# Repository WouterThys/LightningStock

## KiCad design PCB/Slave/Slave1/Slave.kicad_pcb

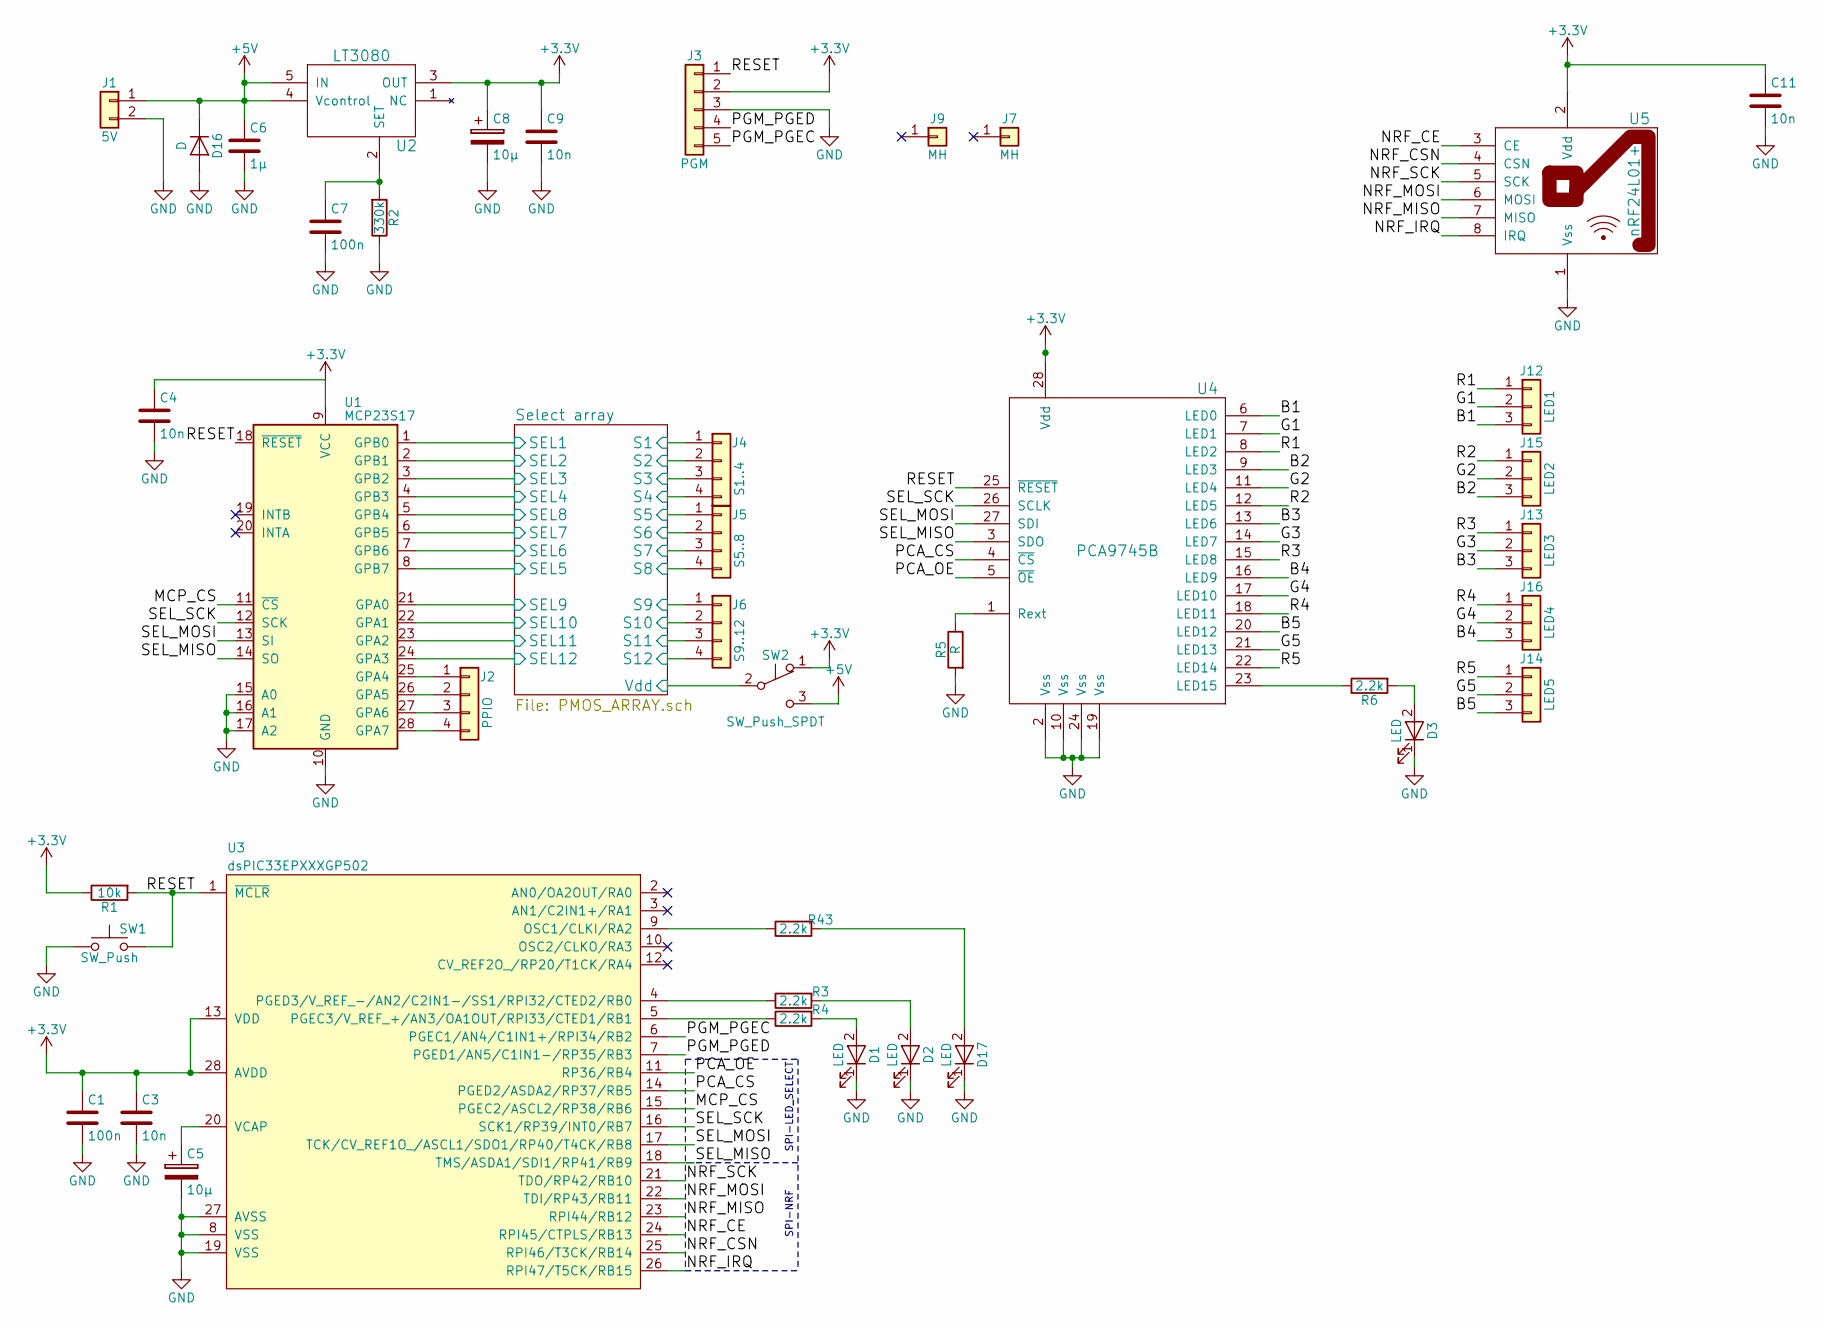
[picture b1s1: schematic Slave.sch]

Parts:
C1, C7: 100n; C_0603_HandSoldering
C3, C4, C9, C11: 10n; C_0603_HandSoldering
C5, C8: 10µ; CP_Tantalum_Case-A_EIA-3216-18_Reflow
C6: 1µ; C_0603_HandSoldering
D1, D2, D3, D17: LED; LED_0603_HandSoldering
D16: D; D_MicroMELF_Hadsoldering
J1: 5V; Pin_Header_Straight_1x02_Pitch2.54mm
J2: PPIO; Pin_Header_Straight_1x04_Pitch2.54mm
J3: PGM; Pin_Header_Angled_1x05_Pitch2.54mm
J4: S1..4; Pin_Header_Straight_1x04_Pitch2.54mm
J5: S5..8; Pin_Header_Straight_1x04_Pitch2.54mm
J6: S9..12; Pin_Header_Straight_1x04_Pitch2.54mm
J7, J9: MH; MountingHole_2.7mm_M2.5_ISO14580_Pad
J12: LED1; Molex_PicoBlade_53047-0310_03x1.25mm_Straight
J13: LED3; Molex_PicoBlade_53047-0310_03x1.25mm_Straight
J14: LED5; Molex_PicoBlade_53047-0310_03x1.25mm_Straight
J15: LED2; Molex_PicoBlade_53047-0310_03x1.25mm_Straight
J16: LED4; Molex_PicoBlade_53047-0310_03x1.25mm_Straight
R1: 10k; R_0603_HandSoldering
R2: 330k; R_0603_HandSoldering
R3, R4, R6, R43: 2.2k; R_0603_HandSoldering
R5: R; R_0603_HandSoldering
SW1: SW_Push; SW_PUSH_6mm
SW2: SW_Push_SPDT; Pin_Header_Straight_1x03_Pitch2.54mm
U1: MCP23S17; SOIC-28W_7.5x17.9mm_Pitch1.27mm
U2: LT3080; TO-220-5_Vertical_StaggeredType1
U3: dsPIC33EPXXXGP502; SOIC-28W_7.5x17.9mm_Pitch1.27mm
U4: PCA9745B; TSSOP-28_4.4x9.7mm_Pitch0.65mm
U5: nRF24L01+; Pin_Header_Straight_2x04_Pitch2.54mm

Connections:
+3V3: C1.1, C3.1, C4.1, C8.1, C9.1, C11.1, J3.2, R1.1, SW2.1 (A), U1.9 (VCC), U2.3 (OUT), U3.13 (VDD), U3.28 (AVDD), U4.28 (Vdd), U5.2 (Vdd); also elsewhere on the board
+5V: C6.1, D16.1 (K), J1.1, SW2.3 (C), U2.4 (Vcontrol), U2.5 (IN); also elsewhere on the board
/B1: J12.3, U4.6 (LED0)
/B2: J15.3, U4.9 (LED3)
/B3: J13.3, U4.13 (LED6)
/B4: J16.3, U4.16 (LED9)
/B5: J14.3, U4.20 (LED12)
/G1: J12.2, U4.7 (LED1)
/G2: J15.2, U4.11 (LED4)
/G3: J13.2, U4.14 (LED7)
/G4: J16.2, U4.17 (LED10)
/G5: J14.2, U4.21 (LED13)
/MCP_CS: U1.11 (~CS), U3.15 (PGEC2/ASCL2/RP38/RB6)
/NRF_CE: U3.24 (RPI45/CTPLS/RB13), U5.3 (CE)
/NRF_CSN: U3.25 (RPI46/T3CK/RB14), U5.4 (CSN)
/NRF_IRQ: U3.26 (RPI47/T5CK/RB15), U5.8 (IRQ)
/NRF_MISO: U3.23 (RPI44/RB12), U5.7 (MISO)
/NRF_MOSI: U3.22 (TDI/RP43/RB11), U5.6 (MOSI)
/NRF_SCK: U3.21 (TDO/RP42/RB10), U5.5 (SCK)
/PCA_CS: U3.14 (PGED2/ASDA2/RP37/RB5), U4.4 (~CS)
/PCA_OE: U3.11 (RP36/RB4), U4.5 (~OE)
/PGM_PGEC: J3.5, U3.6 (PGEC1/AN4/C1IN1+/RPI34/RB2)
/PGM_PGED: J3.4, U3.7 (PGED1/AN5/C1IN1-/RP35/RB3)
/R1: J12.1, U4.8 (LED2)
/R2: J15.1, U4.12 (LED5)
/R3: J13.1, U4.15 (LED8)
/R4: J16.1, U4.18 (LED11)
/R5: J14.1, U4.22 (LED14)
/RESET: J3.1, R1.2, SW1.2, U1.18 (~RESET), U3.1 (~MCLR), U4.25 (~RESET)
/SEL_MISO: U1.14 (SO), U3.18 (TMS/ASDA1/SDI1/RP41/RB9), U4.3 (SDO)
/SEL_MOSI: U1.13 (SI), U3.17 (TCK/CV_REF1O_/ASCL1/SDO1/RP40/T4CK/RB8), U4.27 (SDI)
/SEL_SCK: U1.12 (SCK), U3.16 (SCK1/RP39/INT0/RB7), U4.26 (SCLK)
/Select array/S1: J4.1; also elsewhere on the board
/Select array/S2: J4.2; also elsewhere on the board
/Select array/S3: J4.3; also elsewhere on the board
/Select array/S4: J4.4; also elsewhere on the board
/Select array/S5: J5.1; also elsewhere on the board
/Select array/S6: J5.2; also elsewhere on the board
/Select array/S7: J5.3; also elsewhere on the board
/Select array/S8: J5.4; also elsewhere on the board
/Select array/S9: J6.1; also elsewhere on the board
/Select array/S10: J6.2; also elsewhere on the board
/Select array/S11: J6.3; also elsewhere on the board
/Select array/S12: J6.4; also elsewhere on the board
/Select array/SEL1: U1.1 (GPB0); also elsewhere on the board
/Select array/SEL2: U1.2 (GPB1); also elsewhere on the board
/Select array/SEL3: U1.3 (GPB2); also elsewhere on the board
/Select array/SEL4: U1.4 (GPB3); also elsewhere on the board
/Select array/SEL5: U1.8 (GPB7); also elsewhere on the board
/Select array/SEL6: U1.7 (GPB6); also elsewhere on the board
/Select array/SEL7: U1.6 (GPB5); also elsewhere on the board
/Select array/SEL8: U1.5 (GPB4); also elsewhere on the board
/Select array/SEL9: U1.21 (GPA0); also elsewhere on the board
/Select array/SEL10: U1.22 (GPA1); also elsewhere on the board
/Select array/SEL11: U1.23 (GPA2); also elsewhere on the board
/Select array/SEL12: U1.24 (GPA3); also elsewhere on the board
GND: C1.2, C3.2, C4.2, C5.2, C6.2, C7.2, C8.2, C9.2, C11.2, D1.1 (K), D2.1 (K), D3.1 (K), D16.2 (A), D17.1 (K), J1.2, J3.3, R2.1, R5.2, SW1.1, U1.10 (GND), U1.15 (A0), U1.16 (A1), U1.17 (A2), U3.8 (VSS), U3.19 (VSS), U3.27 (AVSS), U4.2 (Vss), U4.10 (Vss), U4.19 (Vss), U4.24 (Vss), U5.1 (Vss); also elsewhere on the board
unnamed: C5.1, U3.20 (VCAP)
unnamed: C7.1, R2.2, U2.2 (SET)
unnamed: D1.2 (A), R4.2
unnamed: D2.2 (A), R3.2
unnamed: D3.2 (A), R6.2
unnamed: D17.2 (A), R43.2
unnamed: J2.1, U1.25 (GPA4)
unnamed: J2.2, U1.26 (GPA5)
unnamed: J2.3, U1.27 (GPA6)
unnamed: J2.4, U1.28 (GPA7)
unnamed: R3.1, U3.4 (PGED3/V_REF_-/AN2/C2IN1-/SS1/RPI32/CTED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)
unnamed: R4.1, U3.5 (PGEC3/V_REF_+/AN3/OA1OUT/RPI33/CTED1/RB1)
unnamed: R5.1, U4.1 (Rext)
unnamed: R6.1, U4.23 (LED15)
unnamed: R43.1, U3.9 (OSC1/CLKI/RA2)

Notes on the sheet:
SPI-LED_SELECT
SPI-NRF

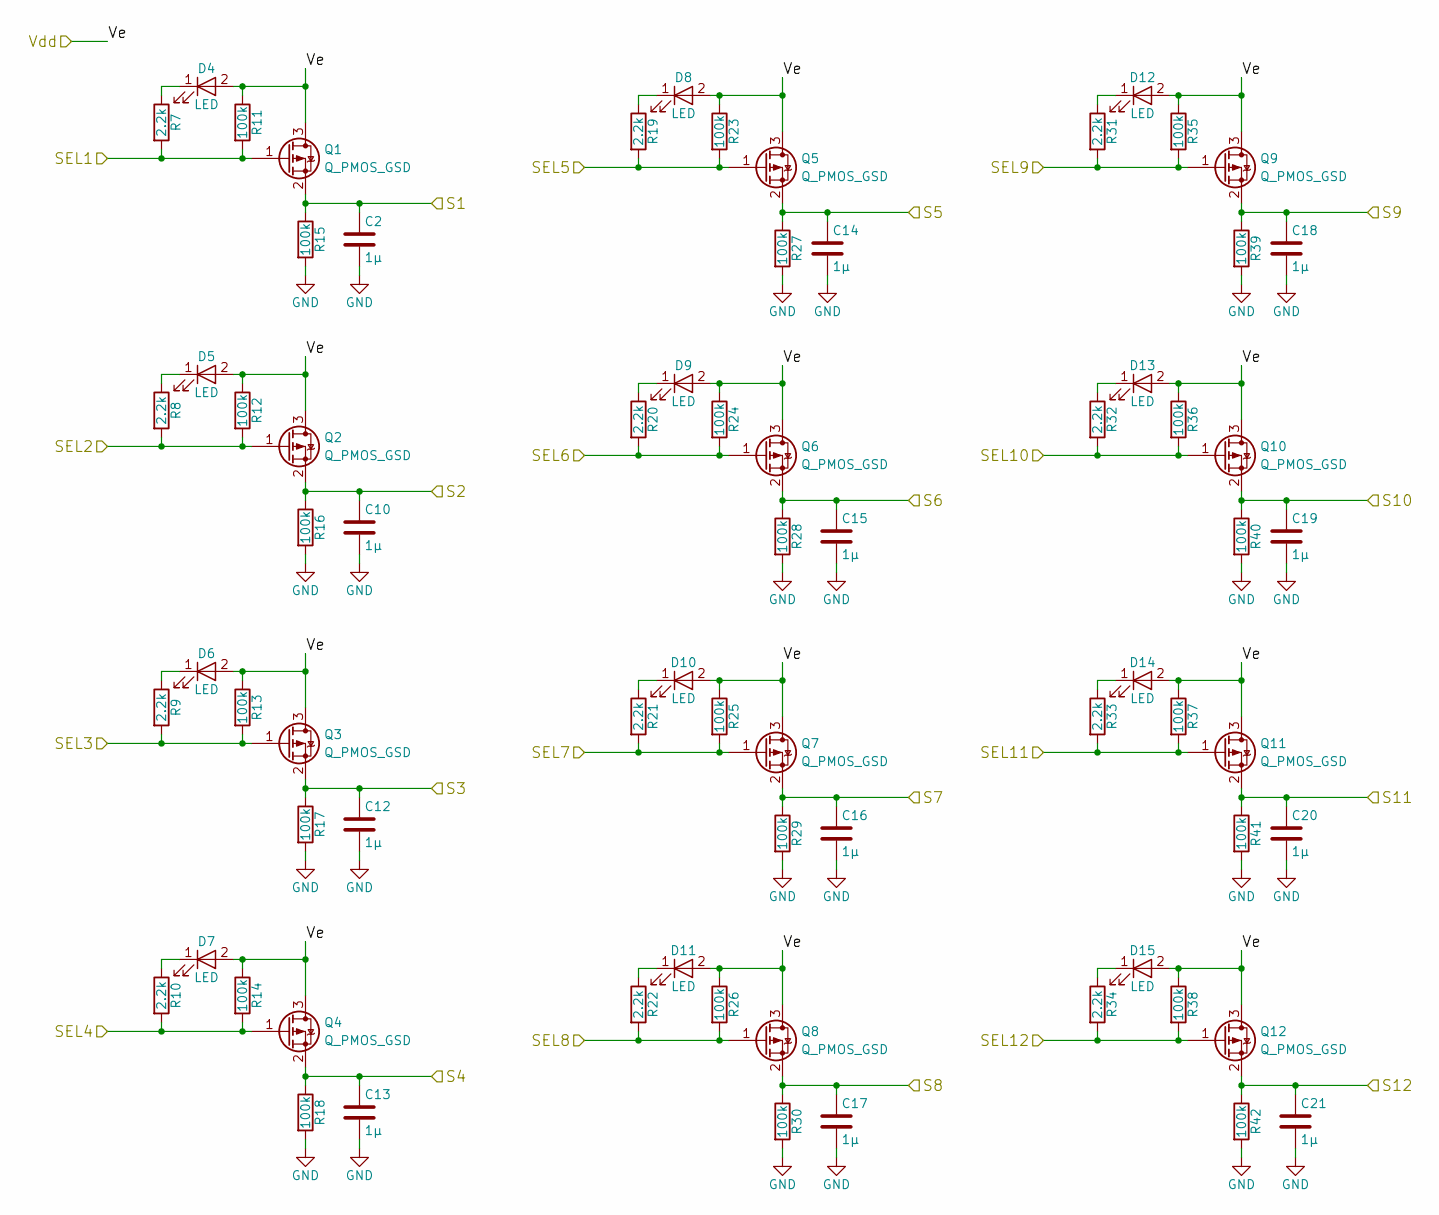
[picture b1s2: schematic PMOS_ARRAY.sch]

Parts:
C2, C10, C12, C13, C14, C15, C16, C17, C18, C19, C20, C21: 1µ; C_0603_HandSoldering
D4, D5, D6, D7, D8, D9, D10, D11, D12, D13, D14, D15: LED; LED_0603_HandSoldering
Q1, Q2, Q3, Q4, Q5, Q6, Q7, Q8, Q9, Q10, Q11, Q12: Q_PMOS_GSD; SOT-323_SC-70_Handsoldering
R7, R8, R9, R10, R19, R20, R21, R22, R31, R32, R33, R34: 2.2k; R_0603_HandSoldering
R11, R12, R13, R14, R15, R16, R17, R18, R23, R24, R25, R26, R27, R28, R29, R30, R35, R36, R37, R38, R39, R40, R41, R42: 100k; R_0603_HandSoldering

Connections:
/Select array/S1: C2.1, Q1.2 (S), R15.1; also elsewhere on the board
/Select array/S2: C10.1, Q2.2 (S), R16.1; also elsewhere on the board
/Select array/S3: C12.1, Q3.2 (S), R17.1; also elsewhere on the board
/Select array/S4: C13.1, Q4.2 (S), R18.1; also elsewhere on the board
/Select array/S5: C14.1, Q5.2 (S), R27.1; also elsewhere on the board
/Select array/S6: C15.1, Q6.2 (S), R28.1; also elsewhere on the board
/Select array/S7: C16.1, Q7.2 (S), R29.1; also elsewhere on the board
/Select array/S8: C17.1, Q8.2 (S), R30.1; also elsewhere on the board
/Select array/S9: C18.1, Q9.2 (S), R39.1; also elsewhere on the board
/Select array/S10: C19.1, Q10.2 (S), R40.1; also elsewhere on the board
/Select array/S11: C20.1, Q11.2 (S), R41.1; also elsewhere on the board
/Select array/S12: C21.1, Q12.2 (S), R42.1; also elsewhere on the board
/Select array/SEL1: Q1.1 (G), R7.2, R11.2; also elsewhere on the board
/Select array/SEL2: Q2.1 (G), R8.2, R12.2; also elsewhere on the board
/Select array/SEL3: Q3.1 (G), R9.2, R13.2; also elsewhere on the board
/Select array/SEL4: Q4.1 (G), R10.2, R14.2; also elsewhere on the board
/Select array/SEL5: Q5.1 (G), R19.2, R23.2; also elsewhere on the board
/Select array/SEL6: Q6.1 (G), R20.2, R24.2; also elsewhere on the board
/Select array/SEL7: Q7.1 (G), R21.2, R25.2; also elsewhere on the board
/Select array/SEL8: Q8.1 (G), R22.2, R26.2; also elsewhere on the board
/Select array/SEL9: Q9.1 (G), R31.2, R35.2; also elsewhere on the board
/Select array/SEL10: Q10.1 (G), R32.2, R36.2; also elsewhere on the board
/Select array/SEL11: Q11.1 (G), R33.2, R37.2; also elsewhere on the board
/Select array/SEL12: Q12.1 (G), R34.2, R38.2; also elsewhere on the board
/Select array/Vdd: D4.2 (A), D5.2 (A), D6.2 (A), D7.2 (A), D8.2 (A), D9.2 (A), D10.2 (A), D11.2 (A), D12.2 (A), D13.2 (A), D14.2 (A), D15.2 (A), Q1.3 (D), Q2.3 (D), Q3.3 (D), Q4.3 (D), Q5.3 (D), Q6.3 (D), Q7.3 (D), Q8.3 (D), Q9.3 (D), Q10.3 (D), Q11.3 (D), Q12.3 (D), R11.1, R12.1, R13.1, R14.1, R23.1, R24.1, R25.1, R26.1, R35.1, R36.1, R37.1, R38.1; also elsewhere on the board
GND: C2.2, C10.2, C12.2, C13.2, C14.2, C15.2, C16.2, C17.2, C18.2, C19.2, C20.2, C21.2, R15.2, R16.2, R17.2, R18.2, R27.2, R28.2, R29.2, R30.2, R39.2, R40.2, R41.2, R42.2; also elsewhere on the board
unnamed: D4.1 (K), R7.1
unnamed: D5.1 (K), R8.1
unnamed: D6.1 (K), R9.1
unnamed: D7.1 (K), R10.1
unnamed: D8.1 (K), R19.1
unnamed: D9.1 (K), R20.1
unnamed: D10.1 (K), R21.1
unnamed: D11.1 (K), R22.1
unnamed: D12.1 (K), R31.1
unnamed: D13.1 (K), R32.1
unnamed: D14.1 (K), R33.1
unnamed: D15.1 (K), R34.1

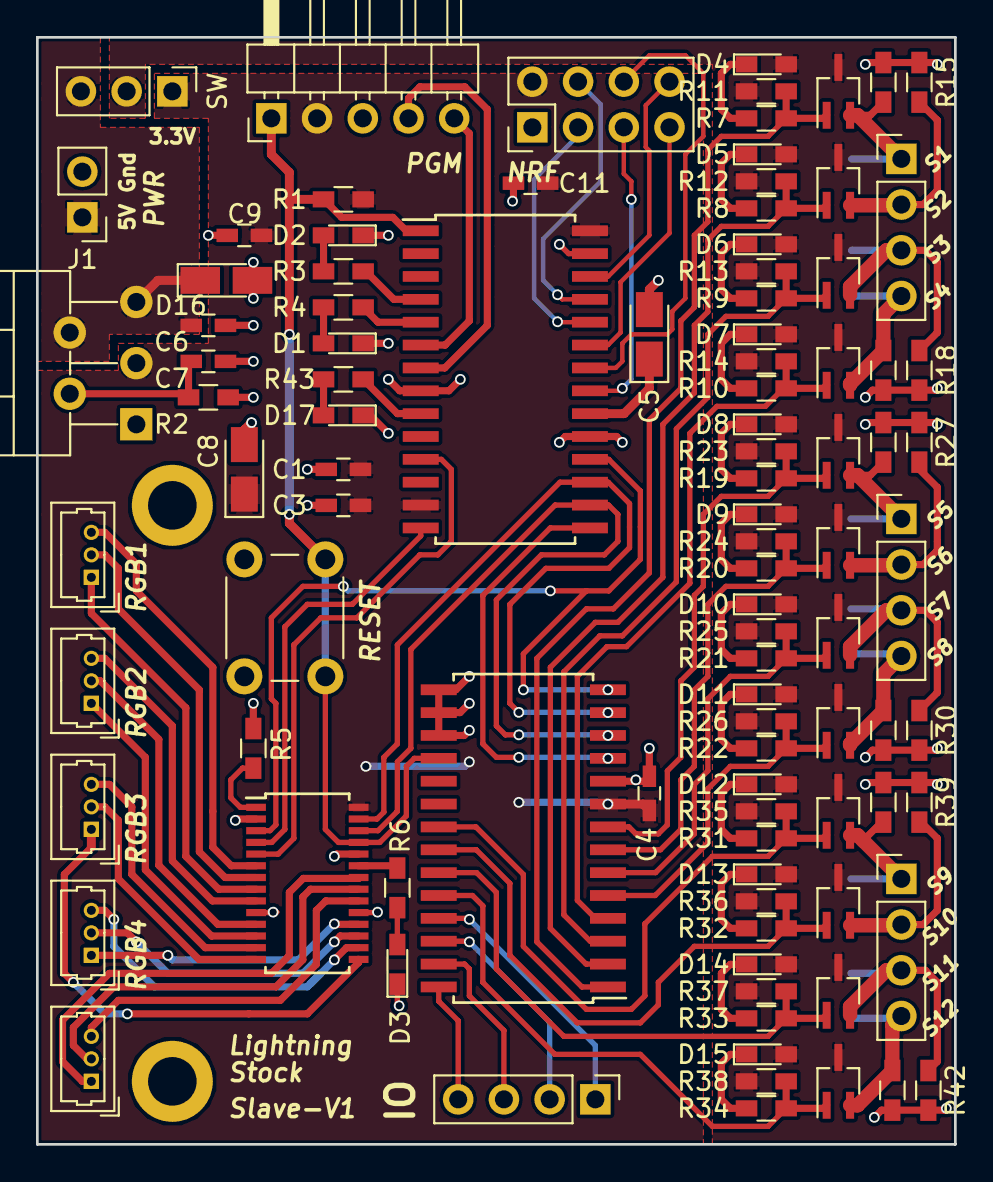
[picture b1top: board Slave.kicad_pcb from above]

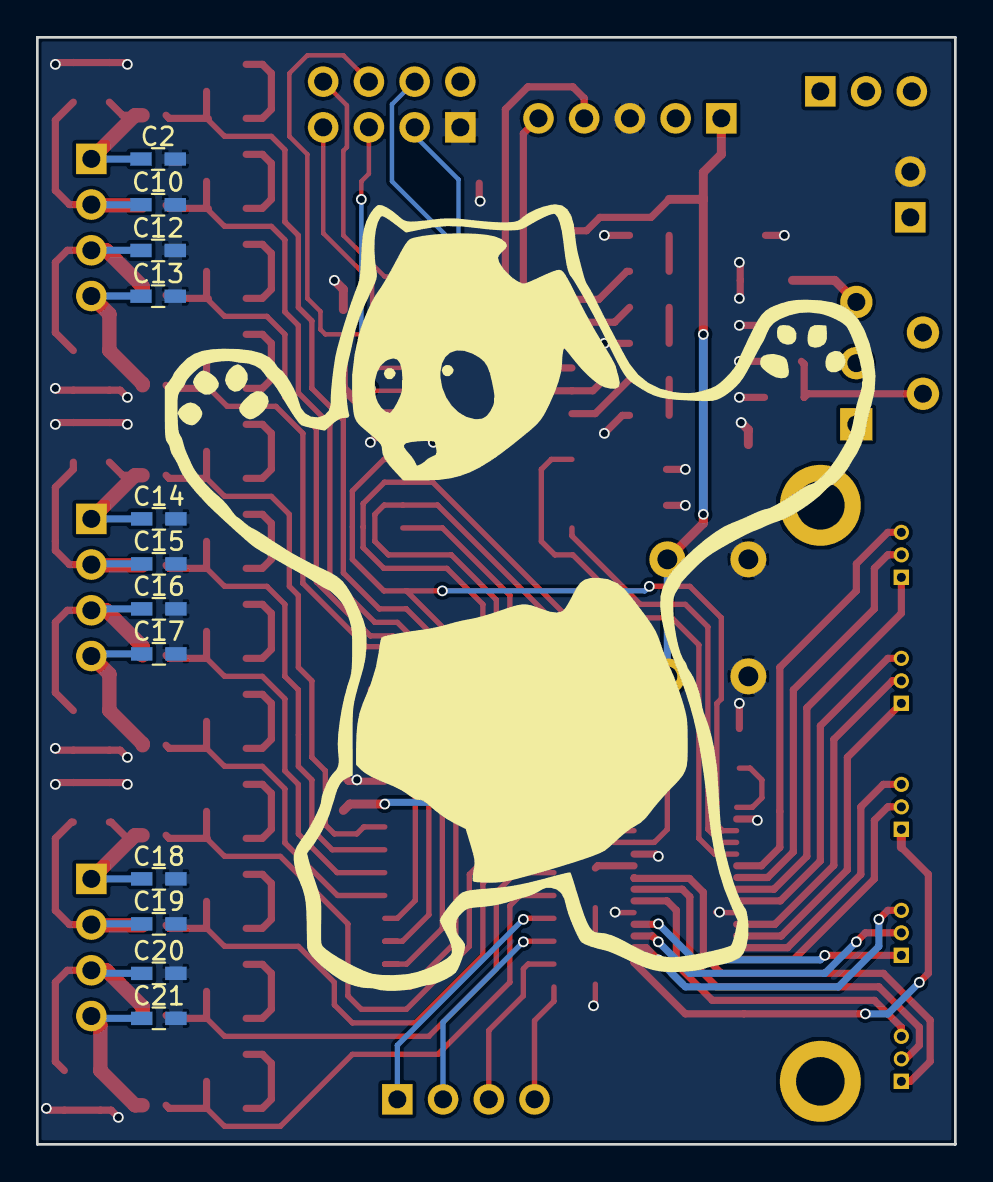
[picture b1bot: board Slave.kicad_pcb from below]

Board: 2 copper layers, 51.0 x 61.5 mm, 113 parts (12 on the bottom side), 85 nets.

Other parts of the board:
SW: SW_Push_SPDT; Pin_Header_Straight_1x03_Pitch2.54mm

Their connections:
+3V3: SW.1; also elsewhere on the board
+5V: SW.3; also elsewhere on the board
/Select array/Vdd: SW.2; also elsewhere on the board

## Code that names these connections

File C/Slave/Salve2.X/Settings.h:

// This is a guard condition so that contents of this file are not included
// more than once.  
#ifndef SETTINGS_H
#define	SETTINGS_H

#define DEBUG       1
    
    
/**
 * Interrupt priorities
 */

#define MI2C_IP     7
#define T3_IP       6    
#define DMA1_IP     5

#define IP_U1RX     3
#define SPI2_IP     2
#define SPI1_IP     4
#define IP_INT1     1


/**
 * LED LOCATIONS
 */
#define LED_ROWS    12
#define LED_COLS    5


    
/**
 *  PIC
 */
 
#define NRF_LINK_LED    LATAbits.LATA0
#define NRF_ERR_LED     LATAbits.LATA1
    

    
/**
 * NRF
 */

#define NRF_CSN         PORTBbits.RB14 
#define NRF_CE          PORTBbits.RB13
#define NRF_IRQ         PORTBbits.RB15

#define NRF_CSN_Dir     TRISBbits.TRISB14
#define NRF_CE_Dir      TRISBbits.TRISB13
#define NRF_IRQ_Dir     TRISBbits.TRISB15


/**
 * MCP23S17
 */
#define MCP_CS          PORTBbits.RB4
#define MCP_CS_Dir      TRISBbits.TRISB4
#define MCP_ADDR        0b01000000


    
/**
 * UART
 */    
#define UART1_BAUD      57600 /* 57600 */
#define UART1_ID        2   

#define UART1_RX_Dir    TRISBbits.TRISB6    /* RX Pin on RP38-RB6             */
#define UART1_TX_Dir    TRISBbits.TRISB5    /* TX Pin on RP37-RB5             */

#define UART1_RX_Map    0b0100110           /* RX on RP38                     */
#define UART1_TX_Map    RPOR1bits.RP37R     /* TX on RP37                     */
    
/**
 * SPI 1
 */    
    
#define SPI1_SCK_Pin    PORTBbits.RB7      /* SCK Pin on RP39-RB7             */
#define SPI1_SCK_Dir    TRISBbits.TRISB7
    
#define SPI1_SDO_Pin    PORTBbits.RB8      /* SDO Pin on RP40-RB8             */
#define SPI1_SDO_Dir    TRISBbits.TRISB8    
    
#define SPI1_SDI_Pin    PORTBbits.RB9      /* SDI Pin on RPI41-RB9            */
#define SPI1_SDI_Dir    TRISBbits.TRISB9        
    
//#define SPI1_SDO_Map    0b001000
//#define SPI1_SCK_Map    0b001001  
//#define SPI1_SDI_Map    44



/**
 * SPI 2
 */    
    
#define SPI2_SCK_Pin    PORTBbits.RB10      /* SCK Pin on RP42-RB10           */
#define SPI2_SCK_Dir    TRISBbits.TRISB10
    
#define SPI2_SDO_Pin    PORTBbits.RB11      /* SDO Pin on RP43-RB11           */
#define SPI2_SDO_Dir    TRISBbits.TRISB11    
    
#define SPI2_SDI_Pin    PORTBbits.RB12      /* SDI Pin on RPI44-RB12          */
#define SPI2_SDI_Dir    TRISBbits.TRISB12       
    
#define SPI2_SDO_Map    0b001000 
#define SPI2_SCK_Map    0b001001  
#define SPI2_SDI_Map    44

    

#endif	/* XC_HEADER_TEMPLATE_H */

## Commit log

2018-06-04 add test file
2018-06-05 slave pcb
2018-06-05 working on the pcb
2018-06-06 created C PIC project for slave
2018-06-06 created master c project
2018-06-06 building slave project
2018-06-07 creating nrf register maps
2018-06-07 deleted test
2018-06-07 getting communication ready with master
2018-06-07 ignore file
2018-06-08 nrf master controller
2018-06-09 master is working
2018-06-09 wireless worksgit status
2018-06-10 salve and master communication
2018-06-11 better slave pcb
2018-06-12 strange xml
2018-06-14 clean up pcb references and text
2018-06-16 MCP IO expander controller
2018-06-16 slave LED controller
2018-07-10 updated pcb for prototype
